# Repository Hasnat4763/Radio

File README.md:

# Akash Chowa DX

Akash Chowa DX is a SW/MW/LW receiver designed based on the Si4735 Radio receiver IC paired with the RP2040 Zero Dev board.

# Why did I build it?

I had an affection towards Radios from childhood. I sometimes try to receive SW stations on my 5$ budget radio I had gotten from a local store. But It does not work that efficiently and I needed a better receiver.
Also the radio I currently have can not demodulate SSB (Single Sideband) and RDS transmitted by modern FM stations. So I designed it to fulfill my own requirements. It also helped me learn new things like impedance control.

# Gallery

Here are some pictures of what I designed

# Schematic

# PCB

# CAD

Base of the case

battery cover

top cover

# BOM (in progress)

| Item                                             | Quantity | Price          | Link |
|--------------------------------------------------|----------|----------------|------|
| Waveshare RP2040 Zero                          | 1        | $5.86          | [Link](https://www.aliexpress.com/item/1005009026492881.html) |
| 1N5819 Diode                                     | 100      | $5.49          | [Link](https://www.aliexpress.com/item/1005010374297754.html) |
| 1N4148 Diode                                     | 100      | $4.43          | [Link](https://www.aliexpress.com/item/1005010373909049.html) |
| SSD1306 OLED Display                             | 1        | $5.33           | [Link](https://www.aliexpress.com/item/1005006141235306.html) |
| EC 11 Encoder with Push Button Half Handle 20MM Shaft | 5 | $6.31 | [Link](https://www.aliexpress.com/item/1005005983134515.html) |
| Si4735 D60 GU | 1 | $15.52  | [Link](https://www.aliexpress.com/item/1005007992766374.html)|
| PE4259 | 20 | $4.96  | [Link](https://www.aliexpress.com/item/32860670352.html)|
| 32.768 kHz Crystal SMD | 10 | $5.01  | [Link](https://www.aliexpress.com/item/1005007548931959.html)|
| CM1213A-01SO | 20 | $6.09  | [Link](https://www.aliexpress.com/item/1005010362089021.html)|
| PAM8302A | 10 | $4.15  | [Link](https://www.aliexpress.com/item/1005011807938839.html)|
| LM4910MM | 5 | $11.43  | [Link](https://www.aliexpress.com/item/1005008963839272.html)|
| 2.5K Ferrite Bead | 100 | $1.63  | [Link](https://www.aliexpress.com/item/1005009841998170.html)|
| 1K Ferrite Bead | 100 | $1.70  | [Link](https://www.aliexpress.com/item/1005009841998170.html)|
| 100uF, 10uF, 100nF, 22pF, 1uF, 0.47uF, 33pF, 18pF, 22nF Capacitor Pack | 720 | $6.21  | [Link](https://www.aliexpress.com/item/1005006124283234.html)|
| 100 ohm Resistor 1206 | 100 | $1.61  | [Link](https://www.aliexpress.com/item/1005011924690352.html)|
| 20k ohm Resistor 1206 | 100 | $1.61  | [Link](https://www.aliexpress.com/item/1005011924690352.html)|
| 100k ohm Resistor 1206 | 100 | $1.61  | [Link](https://www.aliexpress.com/item/1005011924690352.html)|
| SMA connector Edge Mount | 5 | $5.32  | [Link](https://www.aliexpress.com/item/1005007424915378.html)|
| 180nH Inductor 0603 | 100 | $1.33  | [Link](https://www.aliexpress.com/item/1005004900337516.html)|
| 4.7uH Inductor 0603 | 100 | $1.33  | [Link](https://www.aliexpress.com/item/1005004900337516.html)|
| Tactile Switches Push buttons | 20 | $4.12  | [Link](https://www.aliexpress.com/item/1005006046180384.html)|
| 18650 Lithium Battery | 2 | BDT 510 (~$4.16)  | [Link](https://store.roboticsbd.com/battery-charger/983-18650-generic-37v-li-ion-battery-standard-quality-flat-top-solderable-robotics-bangladesh.html)|
| TP4056 BMS | 1 | $4.02 | [Link](https://www.aliexpress.com/item/1005009635476640.html)|
| Rocker Switch | 5 | $5.20  | [Link](https://www.aliexpress.com/item/1005008778176373.html)|
| Binding Post | 5 | $6.00 | [Link](https://www.aliexpress.com/item/1005008274414247.html)|
| Headphone Connector | 10 | $4.45   | [Link](https://www.aliexpress.com/item/32871877936.html)|
| M3 Heat Set Inserts | 30 | $6.13 | [Link](https://www.aliexpress.com/item/1005006071488810.html) |
| M3 Fasteners | 50 | $6.28 | [Link](https://www.aliexpress.com/item/1005011845940916.html) |
| Top Case                                         | 1        | Printing Legion |  |
| Bottom Case                                      | 1        | Printing Legion |  |
| Battery Cover | 1 | Printing Legion | |
| PCB | 5 | $27.67 | JLCPCB |

# Build/Usage Instruction

For impedance control, while ordering from JLCPCB, select the JLC04161H-7628 layer stackup. Also better to import this to the Easyeda Pro and then order as that can get you a few extra discounts.

For ordering parts, you can find most components in LCSC but some components may not be available in LCSC so it needs to be bought from 3rd party stores like aliexpress/alibaba.

For the AM antenna its better to source it from an old broken radio, as its hard to find ferrite antennas online. 

You need a 9:1 Balun to match the impedance of the SMA feed with the long wire antenna you are using.

Never use the Radio while its plugged into the Mains as it introduces extra noise.

For grounding you may be able to just lay the wire parallel to the ground for a few meters.

# Flashing the firmware

To flash the firmware, you first need to add the board to your arduino IDE.

After getting into the Arduino IDE, Go to Preference

Now click on the additional board manager URL and add ```https://github.com/earlephilhower/arduino-pico/releases/download/4.5.2/package_rp2040_index.json```

Now go to boards manager and search RP2040 and download this library

Now you can select the MCU as the waveshare RP2040 zero.

After that you need a few libraries
Si4735 library
Adafruit SSD1306 library
Adafruit GFX library
and the Rotary Encoder Library by Paul Stoffregen

Then you can flash the firmware.

For more details on the Si4735 follow the directions in [Si4735 Arduino Library](https://pu2clr.github.io/SI4735/) here.

# Zine

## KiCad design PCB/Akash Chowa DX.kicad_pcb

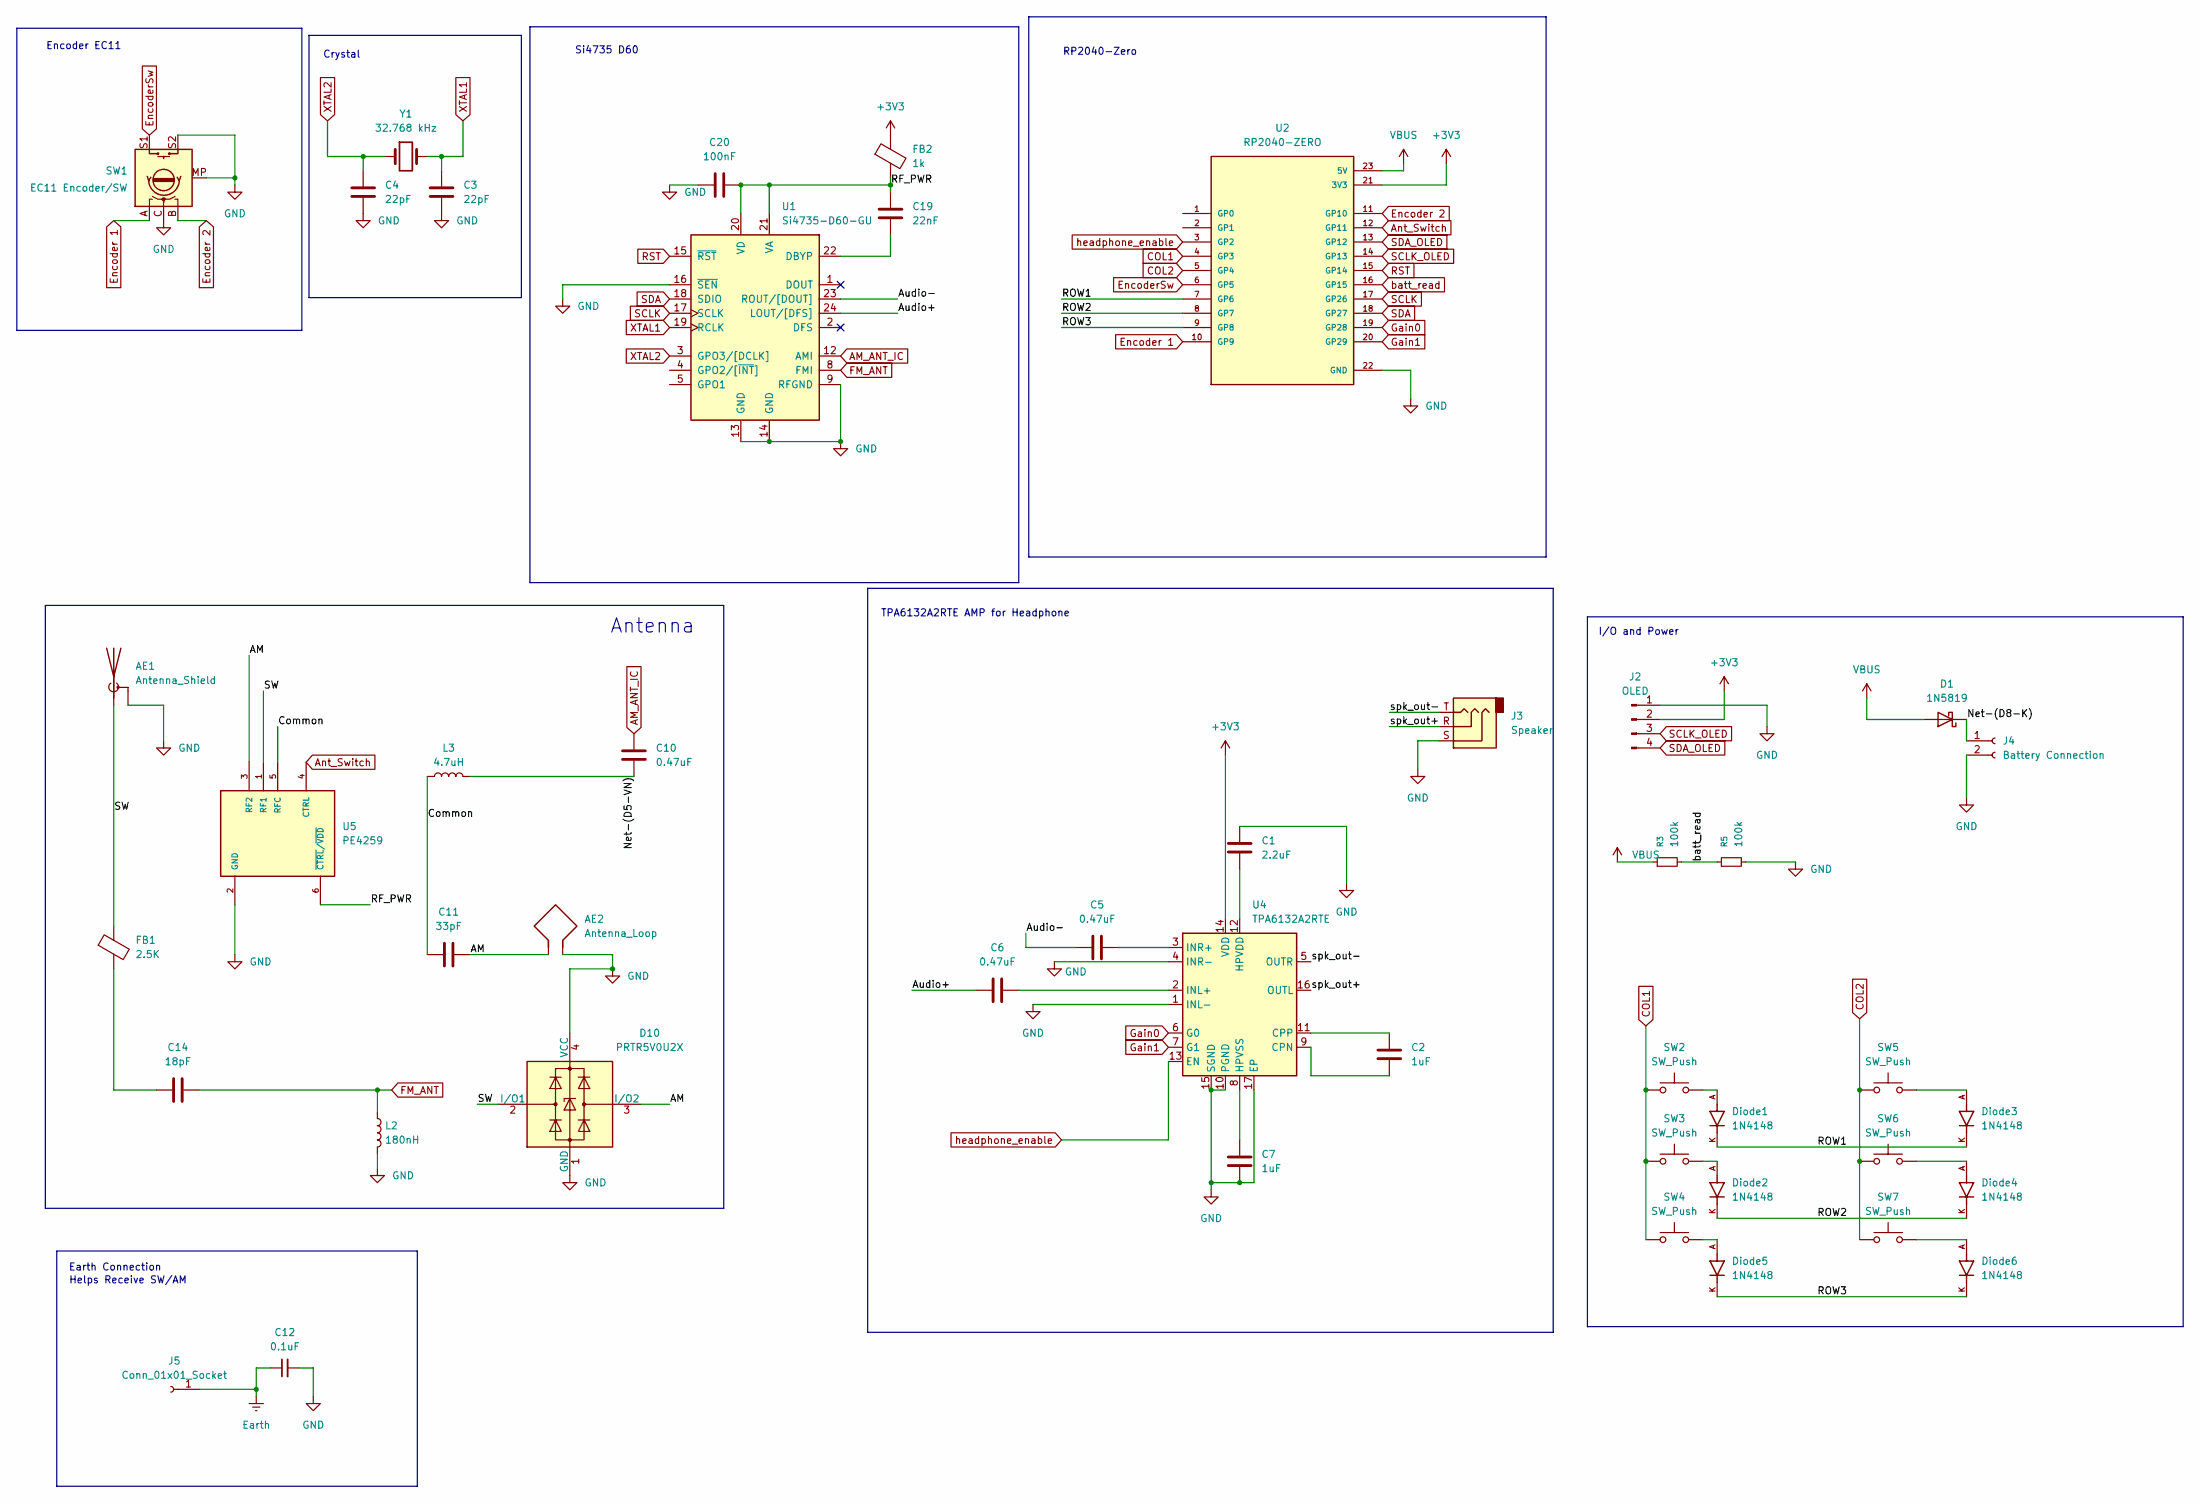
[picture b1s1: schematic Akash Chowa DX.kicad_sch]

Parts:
AE1: Antenna_Shield; SMA_Amphenol_132289_EdgeMount
AE2: Antenna_Loop; PinHeader_1x02_P2.54mm_Vertical
C1: 2.2uF; C_0603_1608Metric_Pad1.08x0.95mm_HandSolder
C2, C7: 1uF; C_0603_1608Metric_Pad1.08x0.95mm_HandSolder
C3, C4: 22pF; C_0603_1608Metric_Pad1.08x0.95mm_HandSolder
C5, C6, C10: 0.47uF; C_0603_1608Metric_Pad1.08x0.95mm_HandSolder
C11: 33pF; C_0603_1608Metric_Pad1.08x0.95mm_HandSolder
C12: 0.1uF; C_0603_1608Metric_Pad1.08x0.95mm_HandSolder
C14: 18pF; C_0603_1608Metric_Pad1.08x0.95mm_HandSolder
C19: 22nF; C_0603_1608Metric_Pad1.08x0.95mm_HandSolder
C20: 100nF; C_0603_1608Metric_Pad1.08x0.95mm_HandSolder
D1: 1N5819; D_DO-41_SOD81_P10.16mm_Horizontal
D10: PRTR5V0U2X; SOT-143
Diode1, Diode2, Diode3, Diode4, Diode5, Diode6: 1N4148; DIOAD753W49L380D172B; PARTREV 5
FB1: 2.5K; R_0805_2012Metric_Pad1.20x1.40mm_HandSolder
FB2: 1k; R_0805_2012Metric_Pad1.20x1.40mm_HandSolder
J2: OLED; MODULE_DM-OLED096-636
J3: Speaker; Jack_3.5mm_CUI_SJ1-3523N_Horizontal
J4: Battery Connection; PinHeader_1x02_P2.54mm_Vertical
J5: Conn_01x01_Socket; PinHeader_1x01_P2.54mm_Vertical
L2: 180nH; L_0603_1608Metric_Pad1.05x0.95mm_HandSolder
L3: 4.7uH; L_0603_1608Metric_Pad1.05x0.95mm_HandSolder
R3, R5: 100k; R_1206_3216Metric_Pad1.30x1.75mm_HandSolder
SW1: EC11 Encoder/SW; RotaryEncoder_Alps_EC11E-Switch_Vertical_H20mm_MountingHoles
SW2, SW3, SW4, SW5, SW6, SW7: SW_Push; SW_FSM8JH
U1: Si4735-D60-GU; SSOP-24_3.9x8.7mm_P0.635mm
U2: RP2040-ZERO; MODULE_RP2040-ZERO; PARTREV NA
U4: TPA6132A2RTE; WQFN-16-1EP_3x3mm_P0.5mm_EP1.6x1.6mm_ThermalVias
U5: PE4259; SOT65P215X110-6N
Y1: 32.768 kHz; Crystal_SMD_0603-2Pin_6.0x3.5mm_HandSoldering

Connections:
+3V3: FB2.1, J2.2, U2.21 (3V3), U4.14 (VDD)
/AM: AE2.1, C11.1, D10.3 (I/O2), U5.3 (RF2)
/Audio+: C6.1, U1.24 (LOUT/[DFS])
/Audio-: C5.1, U1.23 (ROUT/[DOUT])
/Common: C11.2, L3.1, U5.5 (RFC)
/Net-(D5-VN): C10.2, L3.2
/Net-(D8-K): D1.1 (K), J4.1
/RF_PWR: C19.2, C20.1, FB2.2, U1.20 (VD), U1.21 (VA), U5.6 (~CTRL/~VDD)
/ROW1: Diode1.K, Diode3.K, U2.7 (GP6)
/ROW2: Diode2.K, Diode4.K, U2.8 (GP7)
/ROW3: Diode5.K, Diode6.K, U2.9 (GP8)
/SW: AE1.1 (A), D10.2 (I/O1), FB1.1, U5.1 (RF1)
/spk_out+: J3.R, U4.16 (OUTL)
/spk_out-: J3.T, U4.5 (OUTR)
AM_ANT_IC: C10.1, U1.12 (AMI)
Ant_Switch: U2.12 (GP11), U5.4 (CTRL)
COL1: SW2.1, SW3.1, SW4.1, U2.4 (GP3)
COL2: SW5.1, SW6.1, SW7.1, U2.5 (GP4)
Earth: C12.1, J5.1 (Pin_1_1)
Encoder 1: SW1.A, U2.10 (GP9)
Encoder 2: SW1.B, U2.11 (GP10)
EncoderSw: SW1.S1, U2.6 (GP5)
FM_ANT: C14.1, L2.1, U1.8 (FMI)
GND: AE1.2 (Shield), AE2.2, C1.1, C3.1, C4.1, C7.2, C12.2, C20.2, D10.1 (GND), D10.4 (VCC), J2.1, J3.S, J4.2, L2.2, R5.2, SW1.C, SW1.MP, SW1.S2, U1.9 (RFGND), U1.13 (GND), U1.14 (GND), U1.16 (~SEN), U2.22 (GND), U4.1 (INL-), U4.4 (INR-), U4.10 (PGND), U4.15 (SGND), U4.17 (EP), U5.2 (GND)
Gain0: U2.19 (GP28), U4.6 (G0)
Gain1: U2.20 (GP29), U4.7 (G1)
unnamed: C14.2, FB1.2
unnamed: Diode1.A, SW2.2
unnamed: Diode2.A, SW3.2
unnamed: Diode3.A, SW5.2
unnamed: Diode4.A, SW6.2
unnamed: Diode5.A, SW4.2
unnamed: Diode6.A, SW7.2
unnamed: C19.1, U1.22 (DBYP)
unnamed: C2.2, U4.9 (CPN)
unnamed: C2.1, U4.11 (CPP)
unnamed: C1.2, U4.12 (HPVDD)
unnamed: C7.1, U4.8 (HPVSS)
unnamed: C6.2, U4.2 (INL+)
unnamed: C5.2, U4.3 (INR+)
RST: U1.15 (~RST), U2.15 (GP14)
SCLK: U1.17 (SCLK), U2.17 (GP26)
SCLK_OLED: J2.3, U2.14 (GP13)
SDA: U1.18 (SDIO), U2.18 (GP27)
SDA_OLED: J2.4, U2.13 (GP12)
VBUS: D1.2 (A), R3.1, U2.23 (5V)
XTAL1: C3.2, U1.19 (RCLK), Y1.2
XTAL2: C4.2, U1.3 (GPO3/[DCLK]), Y1.1
batt_read: R3.2, R5.1, U2.16 (GP15)
headphone_enable: U2.3 (GP2), U4.13 (EN)

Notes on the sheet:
Antenna
Helps Receive SW/AM
Si4735 D60
RP2040-Zero
Encoder EC11
Earth Connection
I/O and Power
TPA6132A2RTE AMP for Headphone
Crystal

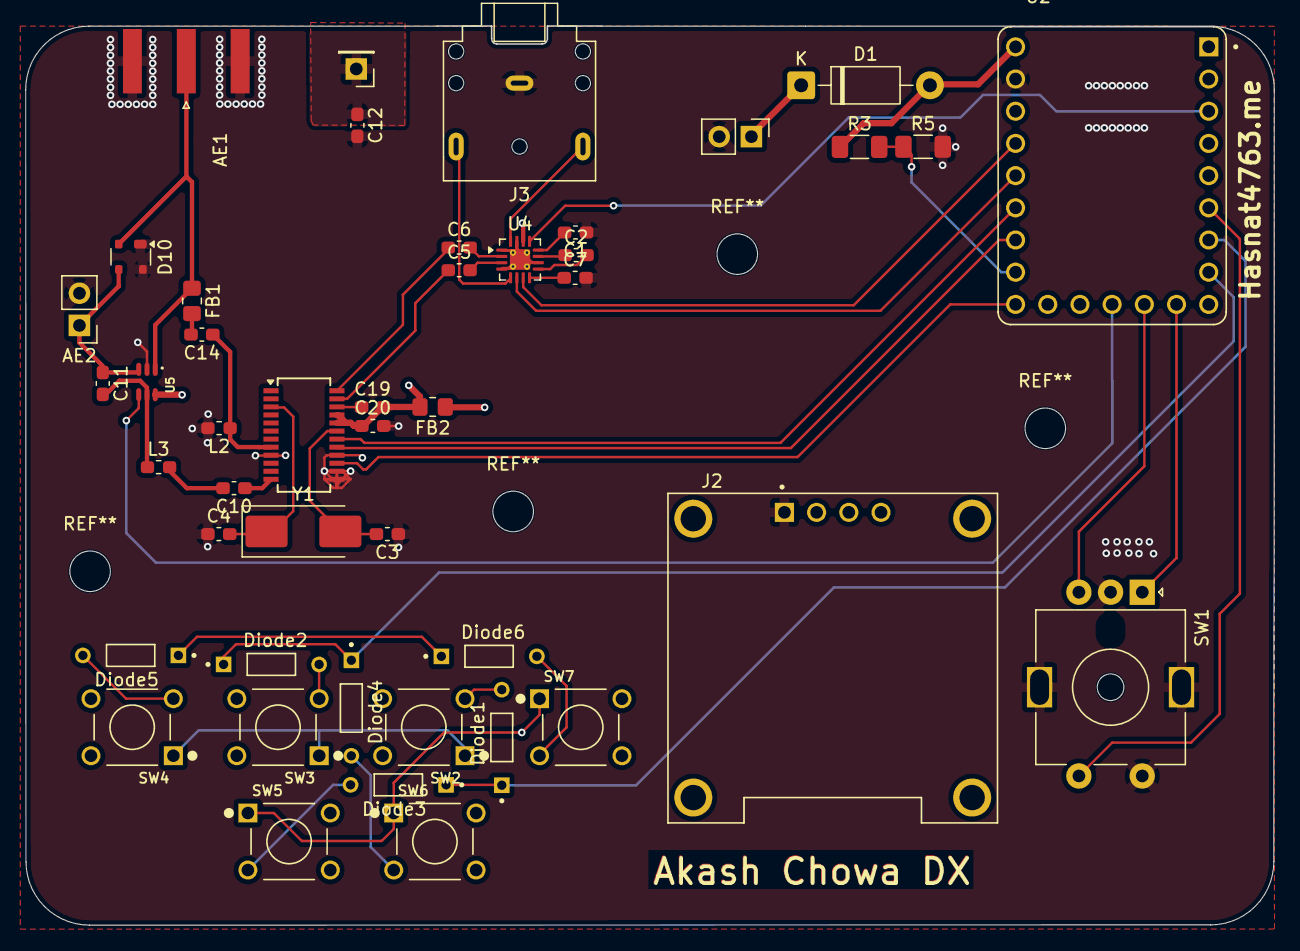
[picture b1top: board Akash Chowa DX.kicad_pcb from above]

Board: 4 copper layers, 98.5 x 70.9 mm, 45 parts (0 on the bottom side), 50 nets.

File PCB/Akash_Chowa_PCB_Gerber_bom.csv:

Designator,Footprint,Quantity,Value,LCSC Part #
AE1,SMA_Amphenol_132289_EdgeMount,1,Antenna_Shield,
AE2,PinHeader_1x02_P2.54mm_Vertical,1,Antenna_Loop,
C1,0603,1,2.2uF,
"C10, C5, C6",0603,3,0.47uF,
C11,0603,1,33pF,
C12,0603,1,0.1uF,
C14,0603,1,18pF,
C19,0603,1,22nF,
"C2, C7",0603,2,1uF,
C20,0603,1,100nF,
"C3, C4",0603,2,22pF,
D1,D_DO-41_SOD81_P10.16mm_Horizontal,1,1N5819,
D10,SOT-143,1,PRTR5V0U2X,
"DIODE1, DIODE2, DIODE3, DIODE4, DIODE5, DIODE6",DIOAD753W49L380D172B,6,1N4148,
FB1,0805,1,2.5K,
FB2,0805,1,1k,
J2,MODULE_DM-OLED096-636,1,OLED,
J3,Jack_3.5mm_CUI_SJ1-3523N_Horizontal,1,Speaker,
J4,PinHeader_1x02_P2.54mm_Vertical,1,Battery Connection,
J5,PinHeader_1x01_P2.54mm_Vertical,1,Conn_01x01_Socket,
L2,0603,1,180nH,
L3,0603,1,4.7uH,
"R3, R5",1206,2,100k,
SW1,RotaryEncoder_Alps_EC11E-Switch_Vertical_H20mm_MountingHoles,1,EC11 Encoder/SW,
"SW2, SW3, SW4, SW5, SW6, SW7",SW_FSM8JH,6,SW_Push,
U1,SSOP-24_3.9x8.7mm_P0.635mm,1,Si4735-D60-GU,
U2,MODULE_RP2040-ZERO,1,RP2040-ZERO,
U4,WQFN-16-1EP_3x3mm_P0.5mm_EP1.6x1.6mm_ThermalVias,1,TPA6132A2RTE,
U5,SOT65P215X110-6N,1,PE4259,
Y1,Crystal_SMD_0603-2Pin_6.0x3.5mm_HandSoldering,1,32.768 kHz,

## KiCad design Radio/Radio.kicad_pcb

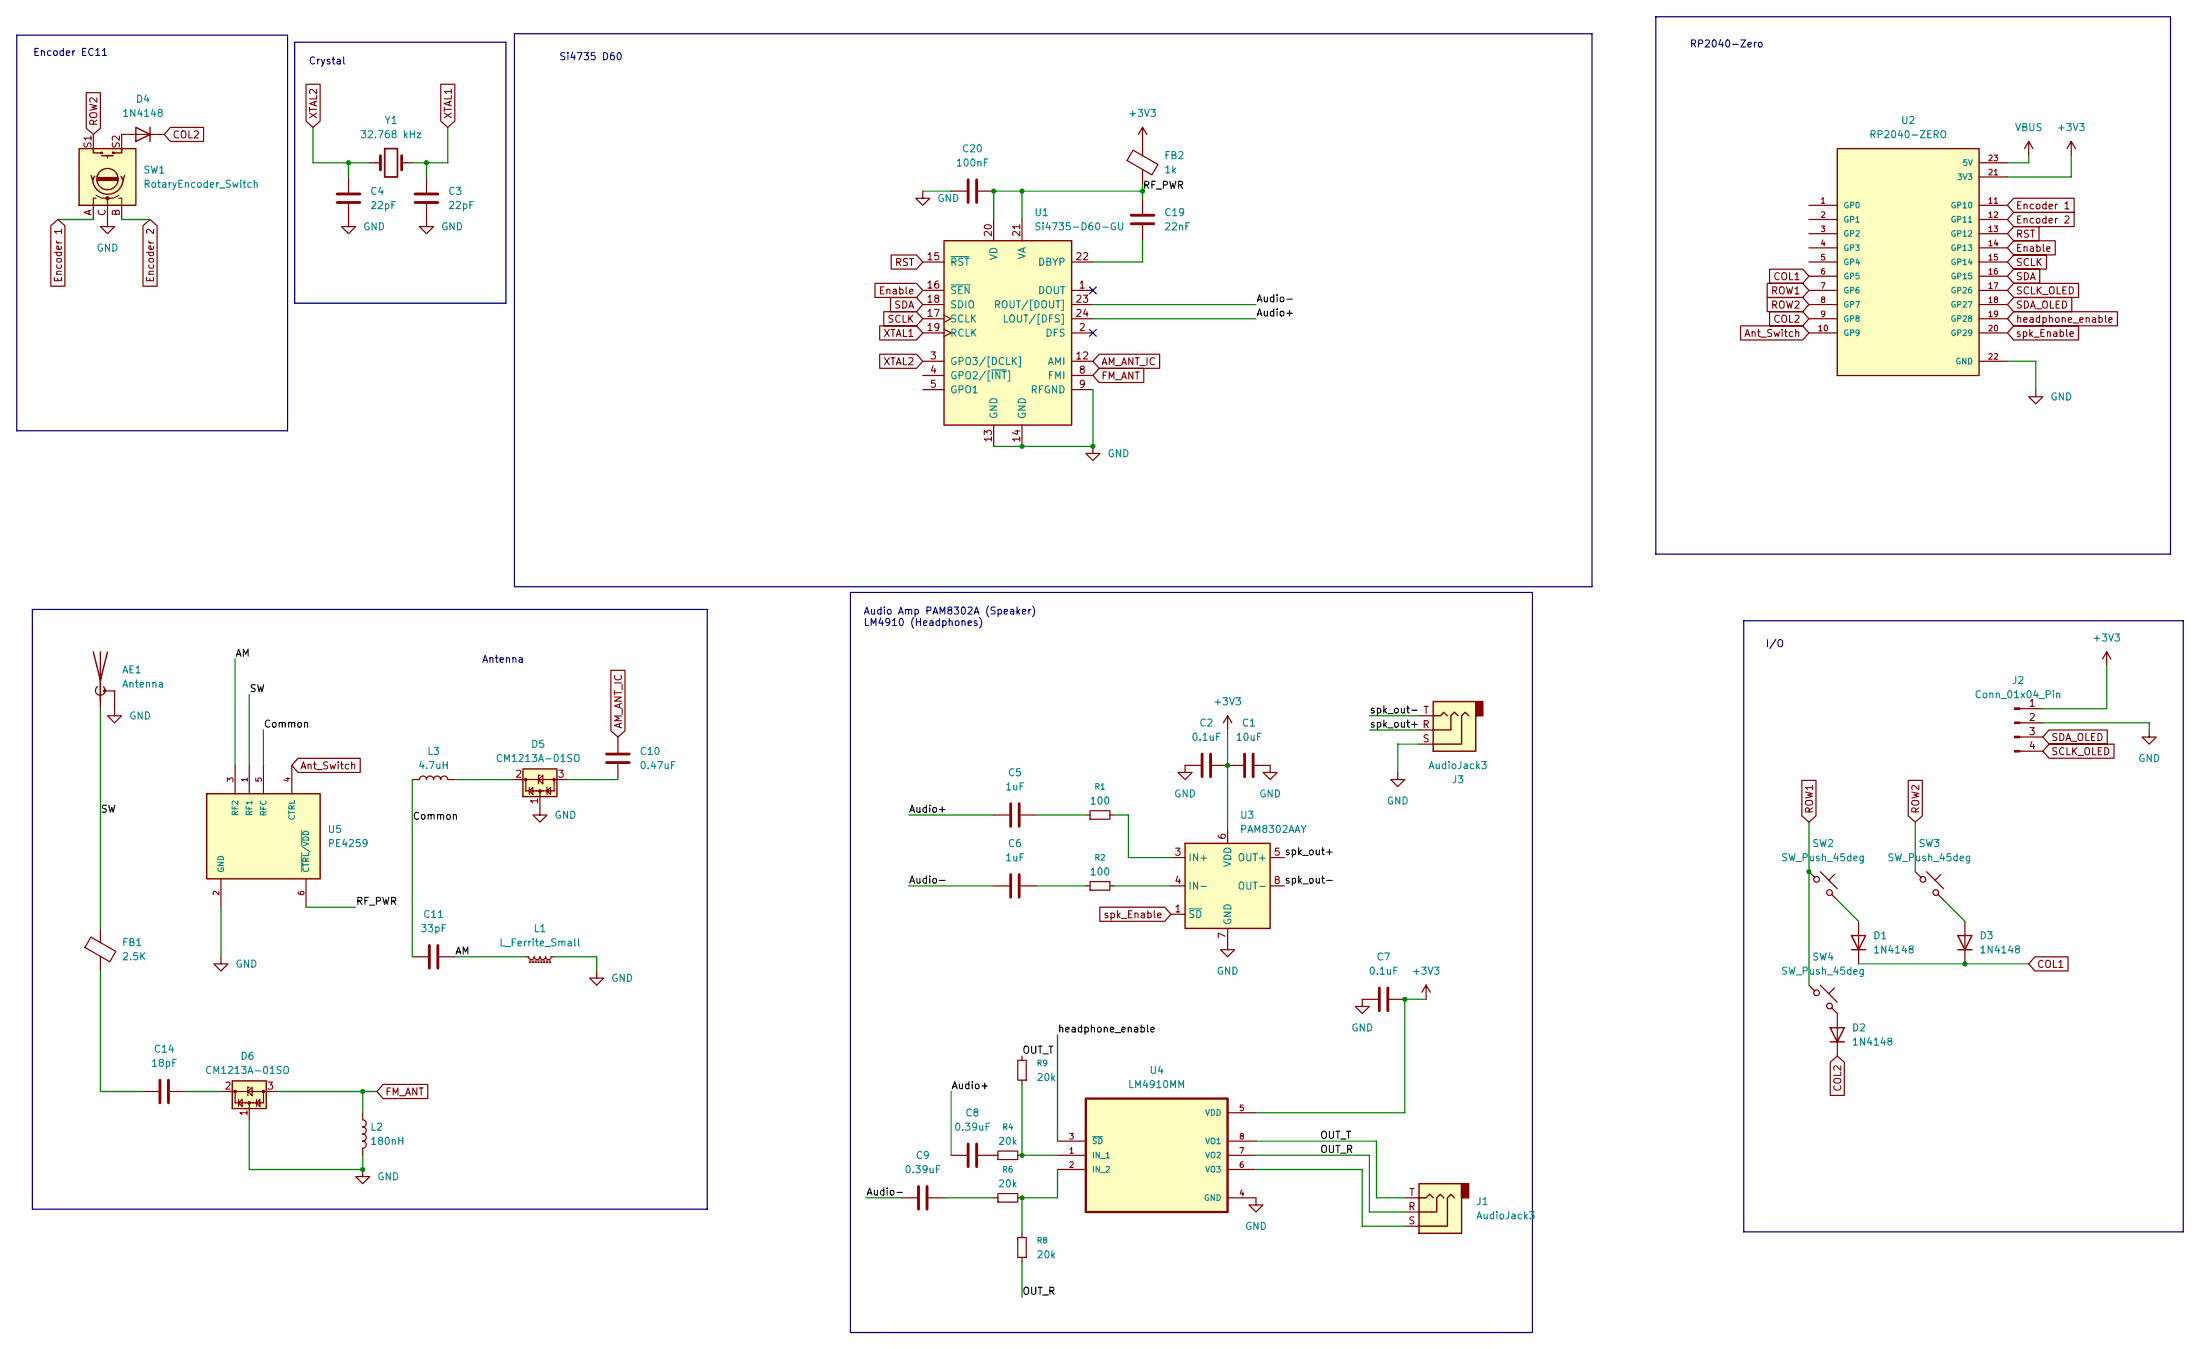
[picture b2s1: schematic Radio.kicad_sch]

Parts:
AE1: Antenna; SMA_Amphenol_901-143_Horizontal
C1: 10uF; C_0603_1608Metric_Pad1.08x0.95mm_HandSolder
C2, C7: 0.1uF; C_0603_1608Metric_Pad1.08x0.95mm_HandSolder
C3, C4: 22pF; C_0603_1608Metric_Pad1.08x0.95mm_HandSolder
C5, C6: 1uF; C_0603_1608Metric_Pad1.08x0.95mm_HandSolder
C8, C9: 0.39uF; C_0603_1608Metric_Pad1.08x0.95mm_HandSolder
C10: 0.47uF; C_0603_1608Metric_Pad1.08x0.95mm_HandSolder
C11: 33pF; C_0603_1608Metric_Pad1.08x0.95mm_HandSolder
C14: 18pF; C_0603_1608Metric_Pad1.08x0.95mm_HandSolder
C19: 22nF; C_0603_1608Metric_Pad1.08x0.95mm_HandSolder
C20: 100nF; C_0603_1608Metric_Pad1.08x0.95mm_HandSolder
D1, D2, D3, D4: 1N4148; D_DO-35_SOD27_P7.62mm_Horizontal
D5, D6: CM1213A-01SO; SOT-23
FB1: 2.5K; R_0805_2012Metric_Pad1.20x1.40mm_HandSolder
FB2: 1k; R_0805_2012Metric_Pad1.20x1.40mm_HandSolder
J1, J3: AudioJack3; Jack_3.5mm_CUI_SJ1-3523N_Horizontal
J2: Conn_01x04_Pin; MODULE_DM-OLED096-636
L1: L_Ferrite_Small; PinHeader_1x02_P2.54mm_Vertical
L2: 180nH; L_0603_1608Metric_Pad1.05x0.95mm_HandSolder
L3: 4.7uH; L_0603_1608Metric_Pad1.05x0.95mm_HandSolder
R1, R2: 100; R_0603_1608Metric_Pad0.98x0.95mm_HandSolder
R4, R6, R8, R9: 20k; R_0603_1608Metric_Pad0.98x0.95mm_HandSolder
SW1: RotaryEncoder_Switch; RotaryEncoder_Alps_EC11E-Switch_Vertical_H20mm_CircularMoun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
SW2, SW3, SW4: SW_Push_45deg; SW_FSM8JH
U1: Si4735-D60-GU; SSOP-24_3.9x8.7mm_P0.635mm
U2: RP2040-ZERO; MODULE_RP2040-ZERO; PARTREV NA
U3: PAM8302AAY; DFN-8-1EP_3x3mm_P0.65mm_EP1.55x2.4mm
U4: LM4910MM; SOP65P490X110-8N
U5: PE4259; SOT65P215X110-6N
Y1: 32.768 kHz; Crystal_SMD_0603-2Pin_6.0x3.5mm_HandSoldering

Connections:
+3V3: C1.1, C2.2, C7.2, FB2.1, J2.1, U2.21 (3V3), U3.6 (VDD), U4.5 (VDD)
/AM: C11.1, L1.2, U5.3 (RF2)
/Audio+: C5.1, C8.1, U1.24 (LOUT/[DFS])
/Audio-: C6.1, C9.1, U1.23 (ROUT/[DOUT])
/Common: C11.2, L3.1, U5.5 (RFC)
/OUT_R: J1.R, R8.1, U4.7 (VO2)
/OUT_T: J1.T, R9.2, U4.8 (VO1)
/RF_PWR: C19.2, C20.1, FB2.2, U1.20 (VD), U1.21 (VA), U5.6 (~CTRL/~VDD)
/SW: AE1.1 (A), FB1.1, U5.1 (RF1)
/spk_out+: J3.R, U3.5 (OUT+)
/spk_out-: J3.T, U3.8 (OUT-)
AM_ANT_IC: C10.1, U1.12 (AMI)
Ant_Switch: U2.10 (GP9), U5.4 (CTRL)
COL1: D1.1 (K), D3.1 (K), U2.6 (GP5)
COL2: D2.1 (K), D4.1 (K), U2.9 (GP8)
Enable: U1.16 (~SEN), U2.14 (GP13)
Encoder 1: SW1.A, U2.11 (GP10)
Encoder 2: SW1.B, U2.12 (GP11)
FM_ANT: D6.3 (VN), L2.1, U1.8 (FMI)
GND: AE1.2 (Shield), C1.2, C2.1, C3.1, C4.1, C7.1, C20.2, D5.1 (CH1), D6.1 (CH1), J2.2, J3.S, L1.1, L2.2, SW1.C, U1.9 (RFGND), U1.13 (GND), U1.14 (GND), U2.22 (GND), U3.7 (GND), U4.4 (GND), U5.2 (GND)
unnamed: C5.2, R1.1
unnamed: C6.2, R2.1
unnamed: C8.2, R4.1
unnamed: C9.2, R6.1
unnamed: C14.2, FB1.2
unnamed: D1.2 (A), SW2.2
unnamed: D2.2 (A), SW4.2
unnamed: D3.2 (A), SW3.2
unnamed: D4.2 (A), SW1.S2
unnamed: C10.2, D5.3 (VN)
unnamed: D5.2 (VP), L3.2
unnamed: C14.1, D6.2 (VP)
unnamed: C19.1, U1.22 (DBYP)
unnamed: R1.2, U3.3 (IN+)
unnamed: R2.2, U3.4 (IN-)
unnamed: R4.2, R9.1, U4.1 (IN_1)
unnamed: R6.2, R8.2, U4.2 (IN_2)
unnamed: J1.S, U4.6 (VO3)
ROW1: SW2.1, SW4.1, U2.7 (GP6)
ROW2: SW1.S1, SW3.1, U2.8 (GP7)
RST: U1.15 (~RST), U2.13 (GP12)
SCLK: U1.17 (SCLK), U2.15 (GP14)
SCLK_OLED: J2.4, U2.17 (GP26)
SDA: U1.18 (SDIO), U2.16 (GP15)
SDA_OLED: J2.3, U2.18 (GP27)
VBUS: U2.23 (5V)
XTAL1: C3.2, U1.19 (RCLK), Y1.2
XTAL2: C4.2, U1.3 (GPO3/[DCLK]), Y1.1
headphone_enable: U2.19 (GP28), U4.3 (~SD)
spk_Enable: U2.20 (GP29), U3.1 (~SD)

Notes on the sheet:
Antenna
Si4735 D60
RP2040-Zero
Encoder EC11
I/O
Audio Amp PAM8302A (Speaker) LM4910 (Headphones)
Crystal

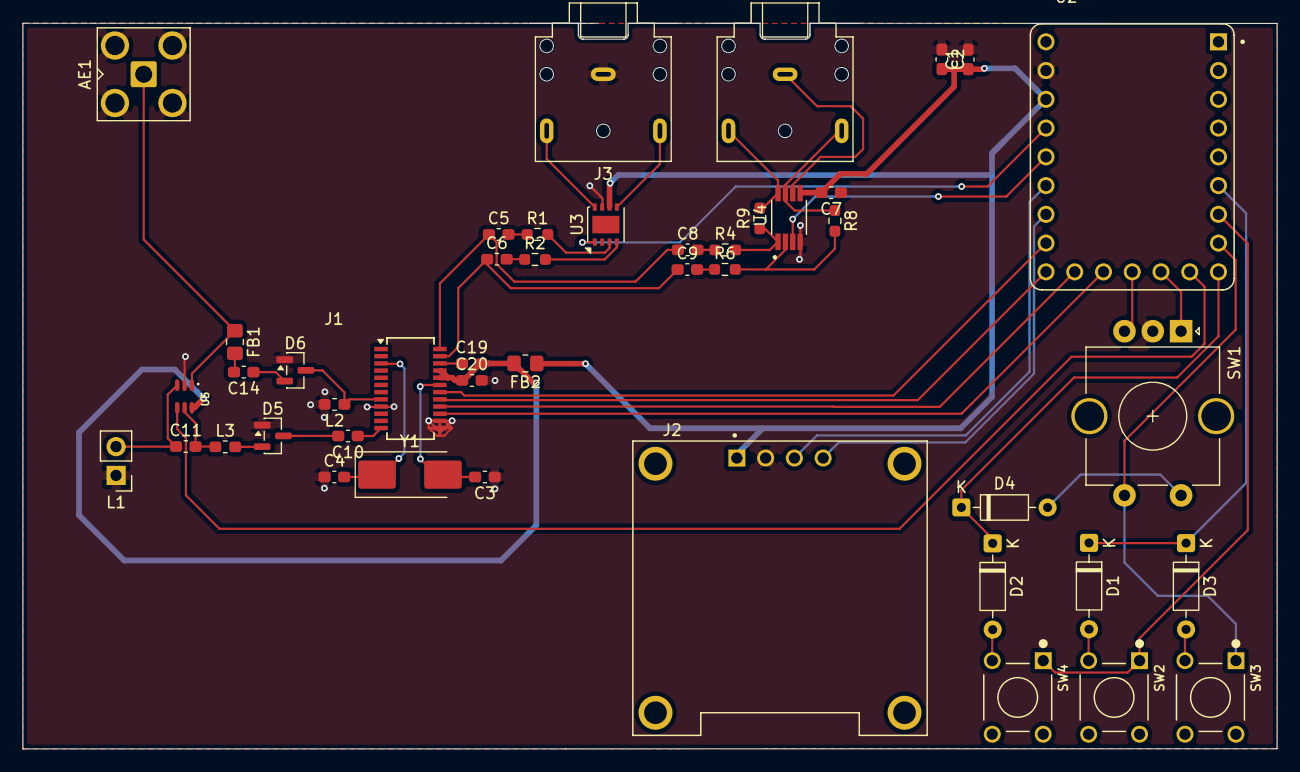
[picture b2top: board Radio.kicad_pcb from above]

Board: 2 copper layers, 110.8 x 64.1 mm, 45 parts (0 on the bottom side), 49 nets.

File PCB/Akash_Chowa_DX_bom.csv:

Designator,Footprint,Quantity,Value,LCSC Part #
AE1,SMA_Amphenol_132289_EdgeMount,1,Antenna_Shield,
AE2,PinHeader_1x02_P2.54mm_Vertical,1,Antenna_Loop,
C1,0603,1,10uF,
"C10, C8, C9",0603,3,0.47uF,
C11,0603,1,33pF,
"C12, C2, C7",0603,3,0.1uF,
C14,0603,1,18pF,
C19,0603,1,22nF,
C20,0603,1,100nF,
"C3, C4",0603,2,22pF,
"C5, C6",0603,2,1uF,
D1,D_DO-41_SOD81_P10.16mm_Horizontal,1,1N5819,
"D2, D3, D4, D7, D8, D9",D_SOD-123F,6,1N4148WT,
"D5, D6",SOT-23,2,CM1213A-01SO,
FB1,0805,1,2.5K,
FB2,0805,1,1k,
J1,Jack_3.5mm_CUI_SJ1-3523N_Horizontal,1,Headset,
J2,MODULE_DM-OLED096-636,1,OLED,
J3,Jack_3.5mm_CUI_SJ1-3523N_Horizontal,1,Speaker,
J4,PinHeader_1x02_P2.54mm_Vertical,1,Battery Connection,
J5,PinHeader_1x01_P2.54mm_Vertical,1,Conn_01x01_Socket,
L2,0603,1,180nH,
L3,0603,1,4.7uH,
"R1, R2",1206,2,100,
"R3, R5",1206,2,100k,
"R4, R6, R8, R9",1206,4,20k,
SW1,RotaryEncoder_Alps_EC11E-Switch_Vertical_H20mm_MountingHoles,1,EC11 Encoder/SW,
"SW2, SW3, SW4, SW5, SW6, SW7",SW_FSM8JH,6,SW_Push,
U1,SSOP-24_3.9x8.7mm_P0.635mm,1,Si4735-D60-GU,
U2,MODULE_RP2040-ZERO,1,RP2040-ZERO,
U3,DFN-8-1EP_3x3mm_P0.65mm_EP1.55x2.4mm,1,PAM8302AAY,
U4,SOP65P490X110-8N,1,LM4910MM,
U5,SOT65P215X110-6N,1,PE4259,
Y1,Crystal_SMD_0603-2Pin_6.0x3.5mm_HandSoldering,1,32.768 kHz,

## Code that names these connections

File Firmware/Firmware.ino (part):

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#define sda_ic            26
#define scl_ic            27
#define rst_ic            14
#define ant_switch        11
#define sda_oled          12
#define scl_oled          13
#define batt_read         15
#define headphone_enable  28
#define speaker_enable    29
#define encoder_sw         5
#define encoder_1          9
#define encoder_2         10

#define COL1               3
#define COL2               4
#define ROW1               6
#define ROW2               7
#define ROW3               8

#define KEY_VOL       0
#define KEY_AUDIO     1
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unsigned long keyPressTime[KEY_COUNT] = {0};
unsigned long lastKeyEvent[KEY_COUNT] = {0};

const uint8_t rowPins[] = {ROW1, ROW2, ROW3};
const uint8_t colPins[] = {COL1, COL2};

long encoderOldPos = -999;
int  encoderDelta  = 0;
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  Wire1.begin();
  Wire1.setClock(100000);

  pinMode(batt_read, INPUT);

  analogReadResolution(12);
  readBattery();
  pinMode(COL1, INPUT_PULLUP);
  pinMode(COL2, INPUT_PULLUP);
  for (int i = 0; i < 3; i++)
    pinMode(rowPins[i], INPUT_PULLUP);
  pinMode(encoder_sw,       INPUT_PULLUP);
  pinMode(speaker_enable,   OUTPUT);
  pinMode(headphone_enable, OUTPUT);
  pinMode(ant_switch,       OUTPUT);

  setSpeaker();
  setAntenna();
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
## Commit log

2025-11-05 Starting
2025-11-05 Update Radio.kicad_sch
    Did basic Schematic
2025-11-06 prepped the base PCB
    This is my 1st RF pcb so I just did the placement for now
    I am gonna consult an engineer later to see what I have wrong
2025-11-10 Update PCB: move components
    Moved several components to new positions. and changed potentiometer footprint
2025-11-12 Update PCB layout and footprints
2026-05-13 Update README
    Added a brief description about the PCB status.
2026-05-19 Updated PCB
2026-05-21 push to git
2026-05-28 Pushing stuff
2026-05-28 Adding More parts to the BOM
2026-05-28 Finished Adding all parts to Bom
2026-05-28 Moving images to a dedicated folder
2026-05-28 Fixed image path issue
2026-05-28 Adding a few remaining items
2026-05-28 Added bom.csv
2026-05-28 Exporter Gerber again
2026-05-28 Fully finishing everything
2026-05-28 Add knob file
2026-05-30 Adding new stuff after changing PCB size
